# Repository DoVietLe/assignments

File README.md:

# assignments
A repository for assignments.

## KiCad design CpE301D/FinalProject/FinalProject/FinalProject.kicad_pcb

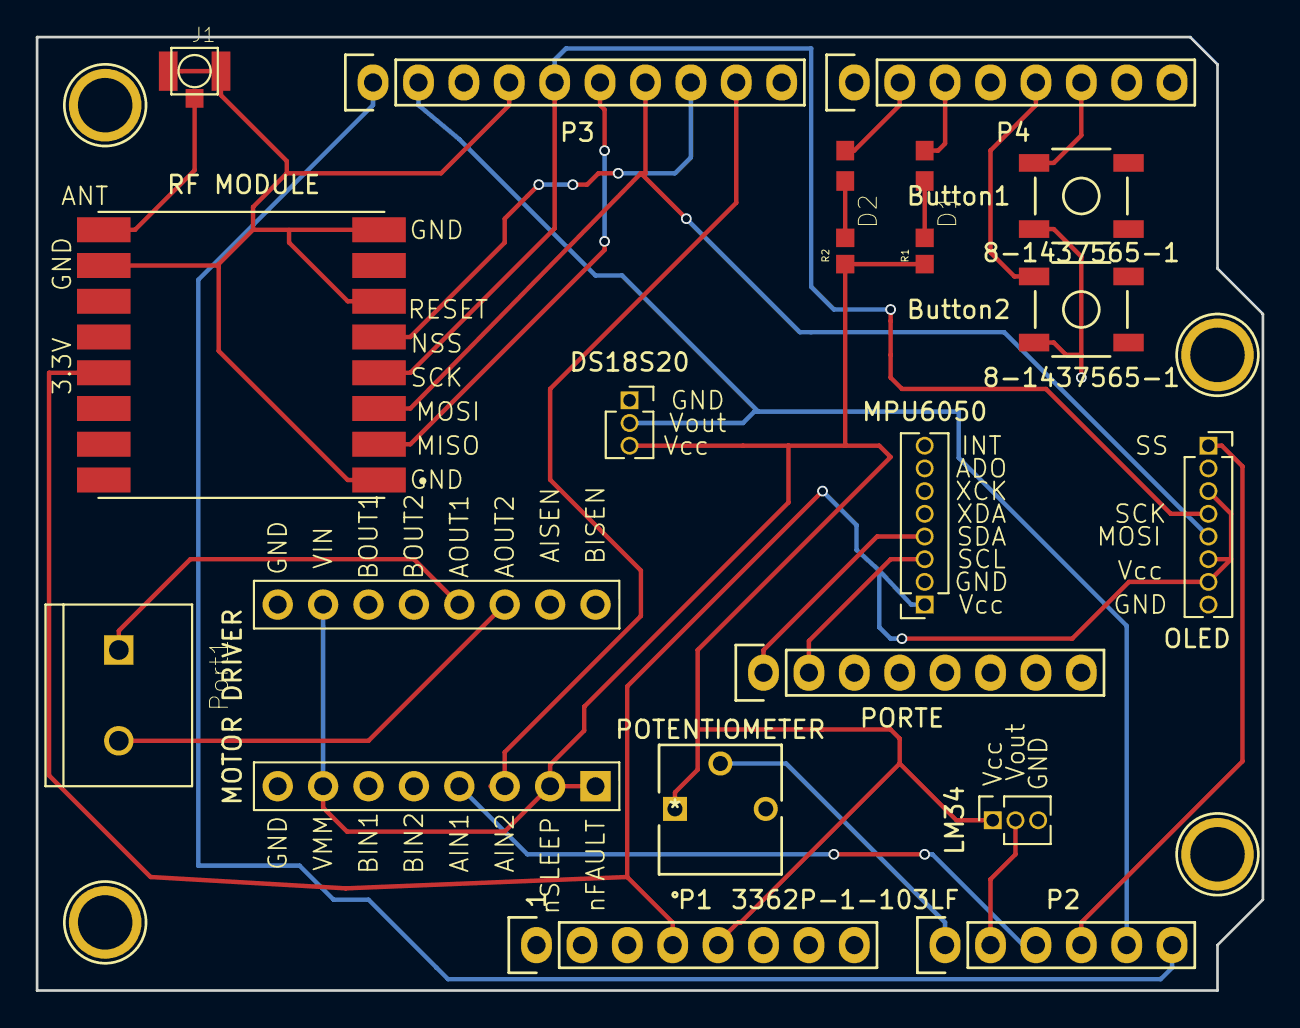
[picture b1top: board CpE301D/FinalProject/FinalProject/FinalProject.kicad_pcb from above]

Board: 2 copper layers, 68.6 x 53.3 mm, 24 parts (0 on the bottom side), 25 nets.

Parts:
Button1, Button2: 8-1437565-1
D1, D2: LTST-C193TGKT-5A; 0603
DS18S20: Conn_01x03_Female; PinSocket_1x03_P1.27mm_Vertical
J1: CONUFL001-SMD; U.FL
LM34: Conn_01x03_Female; PinSocket_1x03_P1.27mm_Vertical
MOTOR DRIVER: Conn_02x08_Counter_Clockwise; MotorDriverFootprint
MPU6050: Conn_01x08_Female; PinSocket_1x08_P1.27mm_Vertical
OLED: Conn_01x08_Female; PinSocket_1x08_P1.27mm_Vertical
P1: Power; Socket_Strip_Arduino_1x08
P2: Analog; Socket_Strip_Arduino_1x06
P3: Digital; Socket_Strip_Arduino_1x10
P4: Digital; Socket_Strip_Arduino_1x08
P5, P6, P7, P8: CONN_01X01; Arduino_1pin
PORTE: Digital; Socket_Strip_Arduino_1x08
POTENTIOMETER: 3362P-1-103LF
Port1: 282837-2; TE_282837-2
R1, R2: RC0603JR-071KL; RESC1607X60N
RF MODULE: RFM95W-915S2; XCVR_RFM95W-915S2

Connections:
+3V3: MPU6050.1, OLED.3, OLED.6, OLED.7, P1.4, RF MODULE.13
+5V: DS18S20.3, LM34.1, MOTOR DRIVER.2, MOTOR DRIVER.7, MOTOR DRIVER.8, MOTOR DRIVER.15, P1.5, POTENTIOMETER.1, R1.1, R2.1
/PB1: MOTOR DRIVER.6, P3.9
/PB2: P3.8, RF MODULE.5
/PB3: OLED.5, P3.7, RF MODULE.3
/PB4: P3.6, RF MODULE.2
/PB5: OLED.4, P3.5, RF MODULE.4
/PC0: P2.1, POTENTIOMETER.2
/PC1: LM34.2, P2.2
/PC2: MOTOR DRIVER.5, P2.3
/PC3: OLED.1, P2.4
/PC4: DS18S20.2, P2.5, P3.2
/PC5: P2.6, P3.1
/PD2: Button1.4, P4.6
/PD3: Button2.4, P4.5
/PD5: D1.1, P4.3
/PD6: D2.1, P4.2
/PE0: MPU6050.4, PORTE.1
/PE1: MPU6050.3, PORTE.2
GND: Button1.2, Button2.2, DS18S20.1, J1.G1, J1.G2, LM34.3, MOTOR DRIVER.1, MOTOR DRIVER.10, MOTOR DRIVER.16, MPU6050.2, OLED.8, P1.6, P1.7, P3.4, POTENTIOMETER.3, RF MODULE.1, RF MODULE.6, RF MODULE.8, RF MODULE.10
unnamed: D1.2, R1.2
unnamed: D2.2, R2.2
unnamed: J1.SIG, RF MODULE.9
unnamed: MOTOR DRIVER.11, Port1.2
unnamed: MOTOR DRIVER.12, Port1.1

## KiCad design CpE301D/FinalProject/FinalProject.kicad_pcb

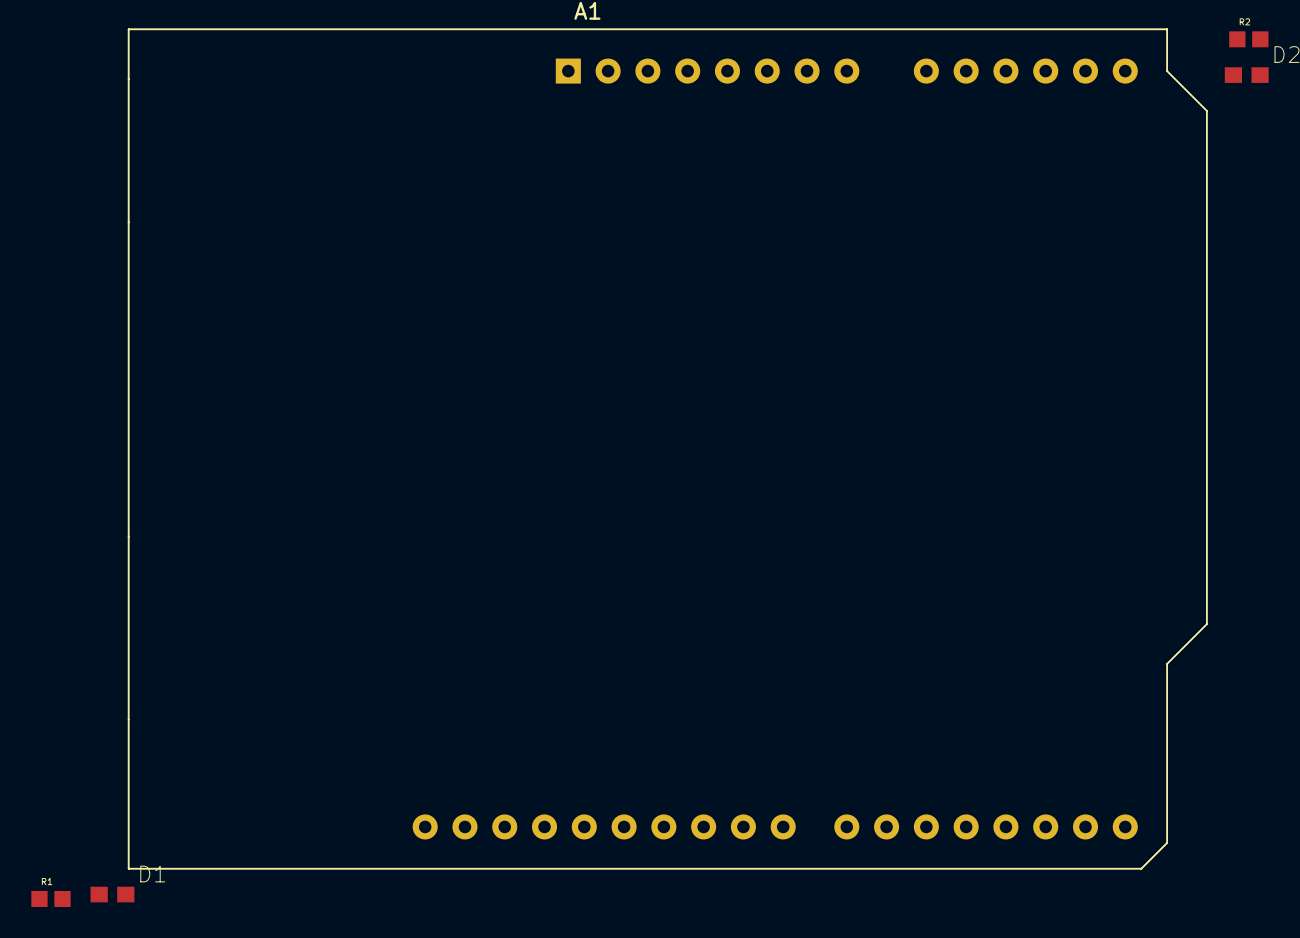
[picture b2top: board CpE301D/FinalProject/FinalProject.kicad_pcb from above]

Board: 2 copper layers, 5 parts (0 on the bottom side), 5 nets, no tracks yet.

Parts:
A1: Arduino_UNO_R3
D1, D2: LTST-C193TGKT-5A; 0603
R1, R2: RC0603JR-071KL; RESC1607X60N

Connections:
GND: D1.1, D2.1
unnamed: A1.20, R1.2
unnamed: A1.21, R2.2
unnamed: D1.2, R1.1
unnamed: D2.2, R2.1

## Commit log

2020-01-29 Changed the readme file.
2020-01-29 Added missing ESD301 file.
2020-01-29 Tested git GUI by adding another folder.
2020-02-12 Added files from assignment 1a. Signed-off-by: unknown <do177@cox.net>
2020-02-13 Finished setting up turn-in.
2020-02-21 Added files from assignment 1b.
2020-02-21 Added github link to assignment 1b to word document.
2020-02-21 Remoted unnecessary texts.
2020-02-26 Uploaded for assignment 2a.
2020-02-26 Added link to assignment to word document.
2020-02-28 Begin adding stuff for assignment 2b.
2020-02-29 Finished design project.
2020-03-07 Added some stuff for assignment 2c.
2020-03-07 Added word document for assignment 2c.
2020-03-12 Added stuff for assignment 3a.
2020-03-12 Added assignment link to word document.
2020-03-15 Added stuff for assignment 3b.
2020-03-15 Added word document.
2020-03-23 Added stuff for midterm.
2020-03-23 Finished midterm documentation.
2020-03-31 Added stuff for assignment 4a.
2020-03-31 Finished documentation.
2020-04-07 Added stuff for assignment 4b and modified names of some files.
2020-04-07 Finished documentation for assignment 4b.
2020-04-19 Added items for Midterm 2 and modified Midterm 1 file names.
2020-04-24 Renamed some files to be more consistent. Added stuff for assignment 5.
2020-04-24 Added assignment link.
2020-04-24 Added video links.
2020-05-01 Started adding stuff for assignment 6.
2020-05-02 Added plots.
2020-05-08 Added PCB Project.
2020-05-08 Removed old project files.

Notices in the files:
parts and their libraries:
Copyright 2016 Accelerated Designs. All rights reserved.
